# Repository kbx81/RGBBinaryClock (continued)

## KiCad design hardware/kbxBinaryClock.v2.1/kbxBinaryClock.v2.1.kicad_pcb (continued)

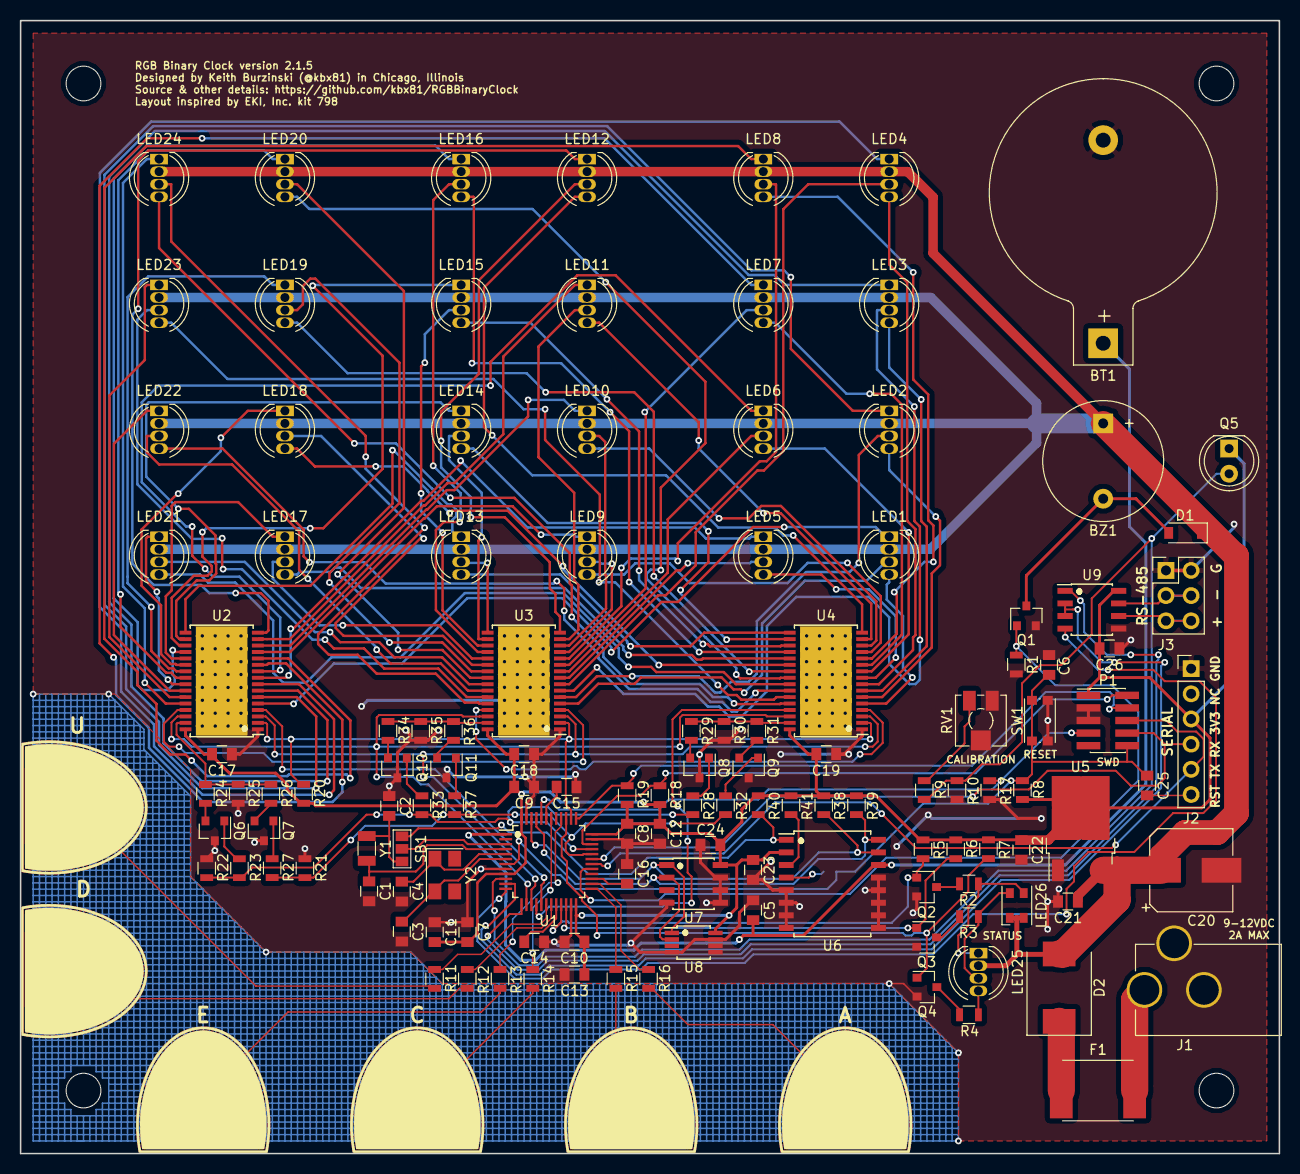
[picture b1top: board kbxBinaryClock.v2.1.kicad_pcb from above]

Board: 2 copper layers, 127.0 x 114.3 mm, 138 parts (1 on the bottom side), 152 nets.

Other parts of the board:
MH1, MH2, MH3, MH4: MountingHole_3.5mm

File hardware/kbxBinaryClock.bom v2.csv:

Reference (v2),Qty,Value,Footprint,Description,Documentation/Vendor
BT1,1,CR2032,Battery_Holders:Keystone_103_1x20mm-CoinCell,Battery cell,http://www.keyelco.com/product.cfm/product_id/719
BZ1,1,Buzzer,Buzzers_Beepers:Buzzer_12x9.5RM7.6,"Buzzer, polar",https://product.tdk.com/en/search/sw_piezo/sw_piezo/em-buzze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
"C1, C2",2,12.5 pF,Capacitors_SMD:C_0805,Unpolarized capacitor,
"C3, C4",2,10 pF,Capacitors_SMD:C_0805,Unpolarized capacitor,
"C5, C6, C8, C9, C10, C17, C18, C19, C21, C23, C24, C25, C26",13,100 nF,Capacitors_SMD:C_0805,Unpolarized capacitor,
C7,1,10 nF,Capacitors_SMD:C_0805,Unpolarized capacitor,
C11,1,1 µF,Capacitors_SMD:C_0805,Unpolarized capacitor,
"C12, C13",2,4.7 µF,Capacitors_SMD:C_0805,Unpolarized capacitor,
"C14, C15, C16",3,47 nF,Capacitors_SMD:C_0805,Unpolarized capacitor,
C20,1,100 µF,Capacitors_SMD:CP_Elec_8x10,Polarised capacitor,https://industrial.panasonic.com/ww/products/capacitors/poly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
C22,1,10 µF,Capacitors_SMD:C_0805,Unpolarized capacitor,
D1,1,1N4148,Diodes_SMD:D_SOD-123,Diode,https://www.diodes.com/assets/Datasheets/ds30086.pdf
D2,1,S3A,Diodes_SMD:D_SMC,,http://www.onsemi.com/pub/Collateral/S3N-D.PDF
F1,1,~2A Polyfuse,Fuse_Holders_and_Fuses:Fuse_SMD2920,"Resettable fuse, polymeric positive temperature coefficient (PPTC)",http://m.littelfuse.com/~/media/electronics/datasheets/reset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
J1,1,Jack-DC,BARREL_JACK,DC_Barrel Jack,
J2,1,Conn_01x06,Pin_Headers:Pin_Header_Straight_1x06_Pitch2.54mm,"Generic connector, single row, 01x06",
J3,1,Conn_02x03_Odd_Even,Pin_Headers:Pin_Header_Straight_2x03_Pitch2.54mm,"Generic connector, double row, 02x03",
"LED1, LED2, LED3, LED4, LED5, LED6, LED7, LED8, LED9, LED10, LED11, LED12, LED13, LED14, LED15, LED16, LED17, LED18, LED19, LED20, LED21, LED22, LED23, LED24, LED25",25,LED_RGB_COMMON_ANODE,LEDs:LED_D5.0mm-4,,https://www.adafruit.com/product/302
LED26,1,LED_Dual_AACC,LEDs:LED_Cree-PLCC4_3.2x2.8mm_CCW,"LED dual, 4-pin",https://www.vcclite.com/product/led-smt-1206-1-72-1v-20ma-re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
P1,1,STM32_SWD_USART,Pin_Headers:Pin_Header_Straight_2x05_Pitch1.27mm_SMD,,https://www.harwin.com/products/M50-3600542R/
"Q1, Q2, Q3, Q4",4,2N7002,TO_SOT_Packages_SMD:SOT-23,"50V Vds, 0.22 A Id, N-channel MOSFET, SOT-23",https://www.diodes.com/assets/Datasheets/ds11303.pdf
Q5,1,Q_Photo_NPN,LEDs:LED_D5.0mm,"Phototransistor NPN, 2-pin (C=1, E=2)",https://www.vishay.com/docs/84768/tept5600.pdf
"Q6, Q7, Q8, Q9, Q10, Q11",6,Q_NPN_BCE,TO_SOT_Packages_SMD:SOT-23,Transistor NPN (general),https://www.diodes.com/assets/Datasheets/ds30036.pdf
"R1, R5, R6, R7, R10",5,1M,Resistors_SMD:R_0805,Resistor,
"R2, R3, R4, R11, R12, R13, R14, R15, R16, R23, R27, R28, R32, R33, R37",15,1K,Resistors_SMD:R_0805,Resistor,
"R8, R9, R17, R18, R19, R20, R21, R22, R26, R31, R36, R40, R41",13,10K,Resistors_SMD:R_0805,Resistor,
"R24, R29, R34",3,4K7,Resistors_SMD:R_0805,Resistor,
"R25, R30, R35",3,24K6,Resistors_SMD:R_0805,Resistor,
"R38, R39",2,3K3,Resistors_SMD:R_0805,Resistor,
RV1,1,100K,Potentiometers:Potentiometer_Trimmer_Vishay_TS53YJ,Potentiometer,http://www.bourns.com/docs/Product-Datasheets/TC33.PDF
SW1,1,SW_Push,Buttons_Switches_SMD:SW_SPST_KMR2,"Push button switch, generic, two pins",https://www.ckswitches.com/media/1479/kmr2.pdf
U1,1,STM32F072CBTx,Housings_QFP:LQFP-48_7x7mm_Pitch0.5mm,Core: ARM Cortex-M0 Package: LQFP48 Flash: 128KB Ram: 16KB Frequency: 48MHz,http://www.st.com/content/ccc/resource/technical/document/da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
"U2, U3, U4",3,TLC5947,Housings_SSOP:HTSSOP-32_6.1x11mm_Pitch0.65mm_ThermalPad,,http://www.ti.com/lit/ds/symlink/tlc5947.pdf
U5,1,LD1117S33TR,TO_SOT_Packages_SMD:TO-252-2,"1A Low Dropout regulator, positive, 1.5V fixed output, SOT-223",http://www.st.com/content/ccc/resource/technical/document/da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
U6,1,DS3231,Housings_SOIC:SOIC-16W_7.5x10.3mm_Pitch1.27mm,Extremely Accurate I2C-Integrated RTC/TCXO/Crystal SOIC-16,https://datasheets.maximintegrated.com/en/ds/DS3231.pdf
U7,1,DS1621,Housings_SOIC:SOIC-8_3.9x4.9mm_Pitch1.27mm,LM75 compatible,https://datasheets.maximintegrated.com/en/ds/DS1621.pdf
U8,1,MCP9804,Housings_SSOP:MSOP-8_3x3mm_Pitch0.65mm,MCP9804/MCP9808,http://ww1.microchip.com/downloads/en/DeviceDoc/25095A.pdf
U9,1,MAX485E,Housings_SOIC:SOIC-8_3.9x4.9mm_Pitch1.27mm,"Half duplex RS-485/RS-422, 2.5 Mbps, ±15kV electro-static discharge (ESD) protection",http://www.st.com/content/ccc/resource/technical/document/da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
Y1,1,32.768 KHz,Crystals:Crystal_SMD_3215-2pin_3.2x1.5mm,Two pin crystal,https://www.ecsxtal.com/store/pdf/ECX-.327-CDX-1293.pdf
Y2,1,8 MHz,Crystals:Crystal_SMD_5032-4pin_5.0x3.2mm,Two pin crystal,http://www.abracon.com/Resonators/abm3b.pdf

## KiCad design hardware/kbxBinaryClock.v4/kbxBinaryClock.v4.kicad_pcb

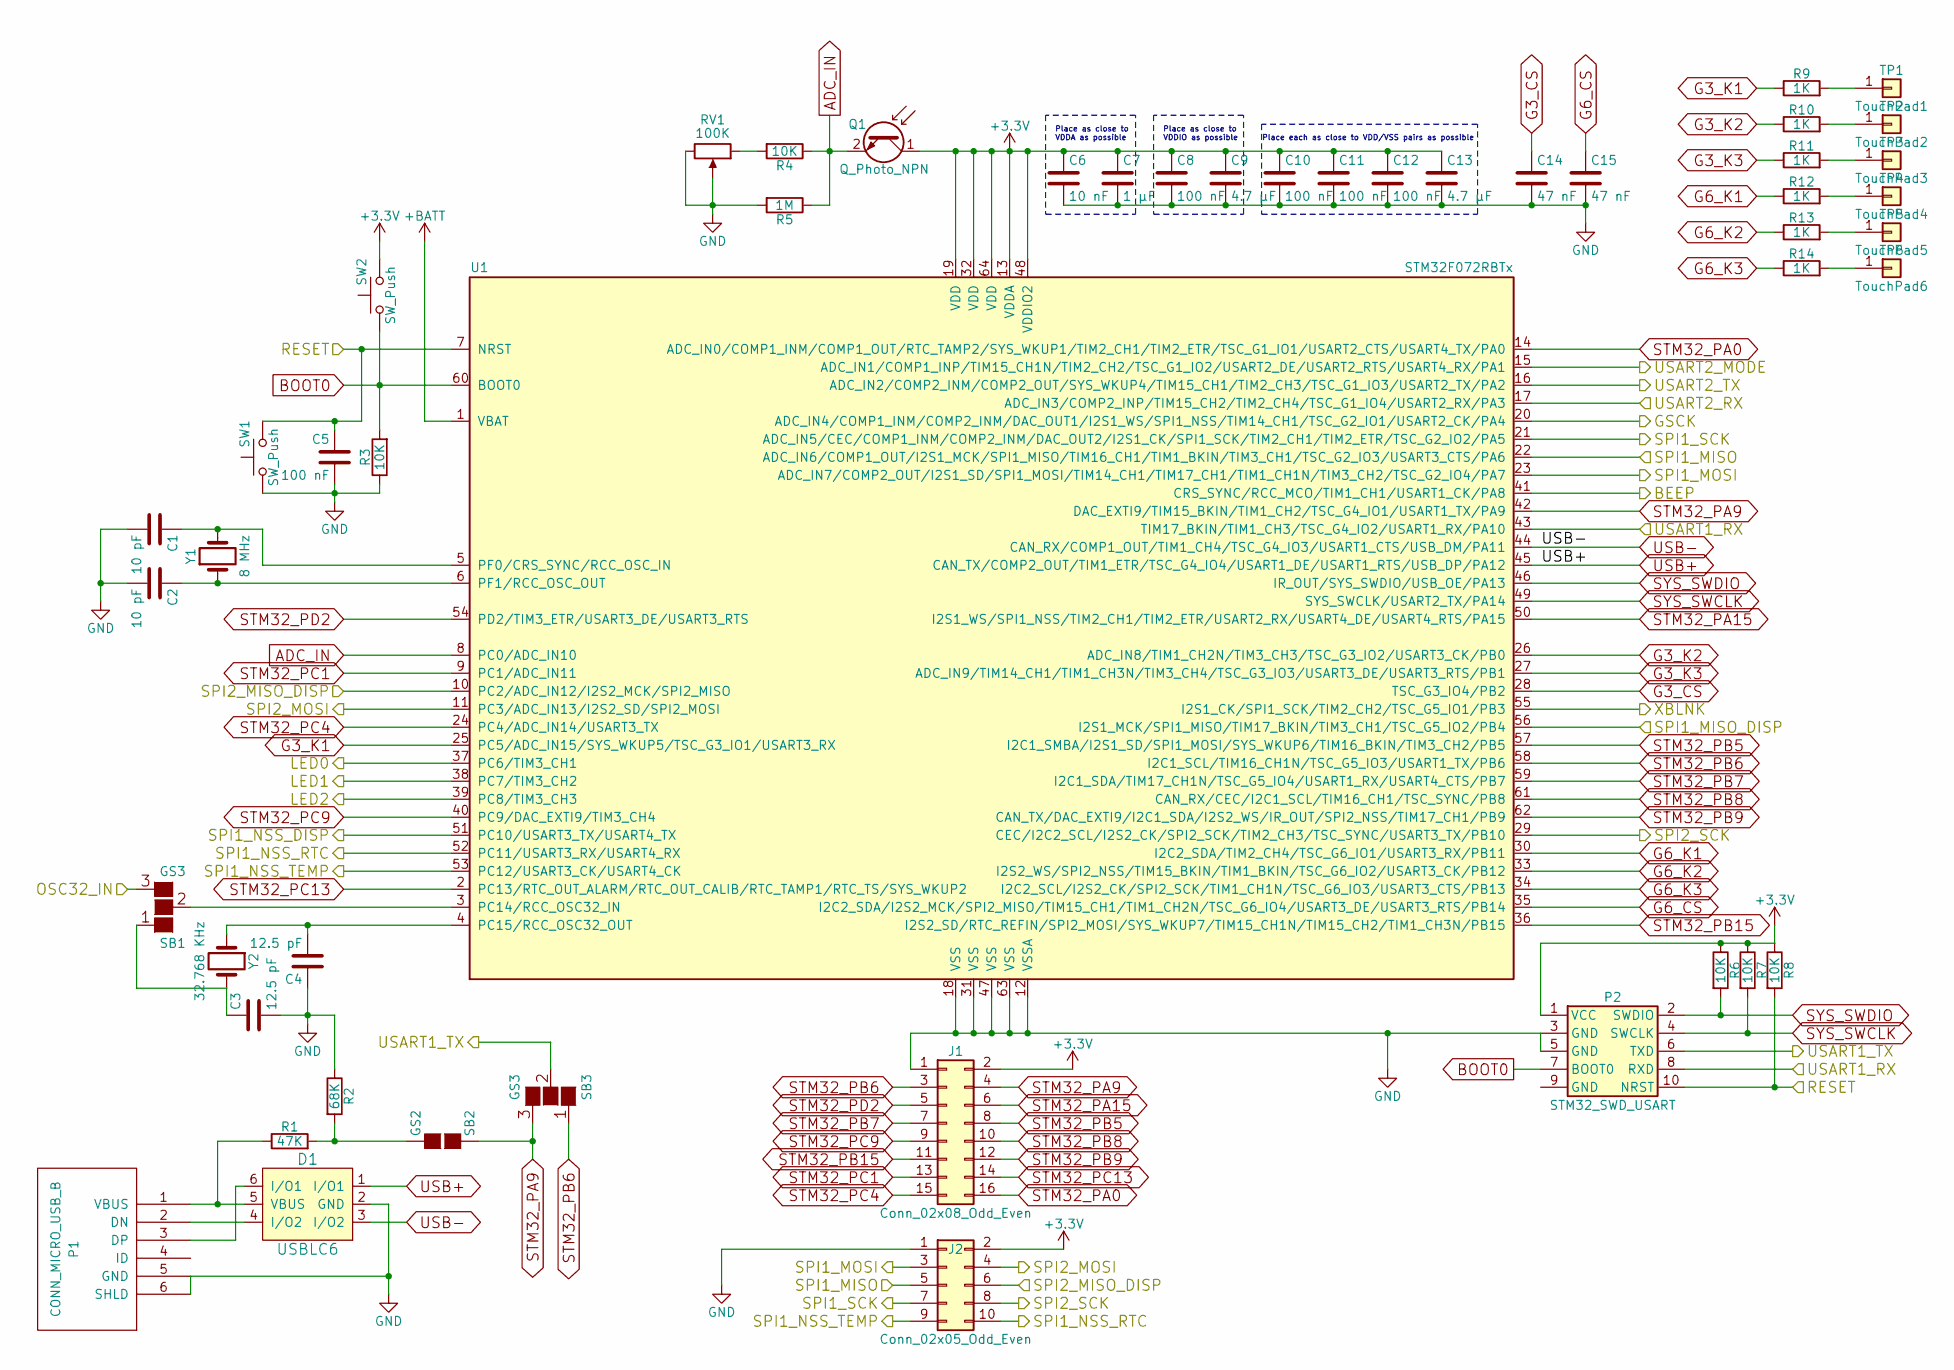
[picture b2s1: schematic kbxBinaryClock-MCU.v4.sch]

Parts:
C1, C2: 10 pF; C_0805
C3, C4: 12.5 pF; C_0805
C5, C8, C10, C11, C12: 100 nF; C_0805
C6: 10 nF; C_0805
C7: 1 µF; C_0805
C9, C13: 4.7 µF; C_0805
C14, C15: 47 nF; C_0805
D1: USBLC6; SOT-23-6
J1: Conn_02x08_Odd_Even; Pin_Header_Straight_2x08_Pitch2.54mm
J2: Conn_02x05_Odd_Even; Pin_Header_Straight_2x05_Pitch2.54mm
P1: CONN_MICRO_USB_B; USB_Micro-B_Molex-105017-0001
P2: STM32_SWD_USART; Pin_Header_Straight_2x05_Pitch1.27mm_SMD; Part Number M50-3600542R
Q1: Q_Photo_NPN; LED_D5.0mm; Part Number TEPT5600
R1: 47K; R_0805
R2: 68K; R_0805
R3, R4, R6, R7, R8: 10K; R_0805
R5: 1M; R_0805
R9, R10, R11, R12, R13, R14: 1K; R_0805
RV1: 100K; Potentiometer_Trimmer_Vishay_TS53YJ; Part Number TC33X-2-104E
SB1, SB3: GS3
SB2: GS2
SW1, SW2: SW_Push; SW_SPST_KMR2; Part Number KMR221G LFS
TP1: TouchPad1
TP2: TouchPad2; TouchPad1
TP3: TouchPad3; TouchPad1
TP4: TouchPad4; TouchPad1
TP5: TouchPad5; TouchPad1
TP6: TouchPad6; TouchPad1
U1: STM32F072RBTx; LQFP-64_10x10mm_Pitch0.5mm
Y1: 8 MHz; Crystal_SMD_5032-4pin_5.0x3.2mm; Part Number ABM3B-8.000MHZ-10-1UT
Y2: 32.768 KHz; Crystal_SMD_3215-2pin_3.2x1.5mm; Part Number ECX-.327-CDX-1293

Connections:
+3V3: C6.1, C7.1, C8.1, C9.1, C10.1, C11.1, C12.1, C13.1, J1.2, J2.2, P2.1 (VCC), Q1.1 (C), R6.1, R7.1, R8.1, SW2.2, U1.13 (VDDA), U1.19 (VDD), U1.32 (VDD), U1.48 (VDDIO2), U1.64 (VDD); also elsewhere on the board
+BATT: U1.1 (VBAT); also elsewhere on the board
/Display/GSCK: U1.20 (ADC_IN4/COMP1_INM/COMP2_INM/DAC_OUT1/I2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); also elsewhere on the board
/Display/SPI1_MISO_DISP: U1.56 (I2S1_MCK/SPI1_MISO/TIM17_BKIN/TIM3_CH1/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); also elsewhere on the board
/Display/SPI1_MOSI: J2.3, U1.23 (ADC_IN7/COMP2_OUT/I2S1_SD/SPI1_MOSI/TIM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); also elsewhere on the board
/Display/SPI1_NSS_DISP: U1.51 (PC10/USART3_TX/USART4_TX); also elsewhere on the board
/Display/SPI1_SCK: J2.7, U1.21 (ADC_IN5/CEC/COMP1_INM/COMP2_INM/DAC_OUT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); also elsewhere on the board
/Display/SPI2_MISO_DISP: J2.6, U1.10 (PC2/ADC_IN12/I2S2_MCK/SPI2_MISO); also elsewhere on the board
/Display/SPI2_MOSI: J2.4, U1.11 (PC3/ADC_IN13/I2S2_SD/SPI2_MOSI); also elsewhere on the board
/Display/SPI2_SCK: J2.8, U1.29 (CEC/I2C2_SCL/I2S2_CK/SPI2_SCK/TIM2_CH3/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); also elsewhere on the board
/Display/XBLNK: U1.55 (I2S1_CK/SPI1_SCK/TIM2_CH2/TSC_G5_IO1/PB3); also elsewhere on the board
/MCU/BEEP: U1.41 (CRS_SYNC/RCC_MCO/TIM1_CH1/USART1_CK/PA8); also elsewhere on the board
/MCU/LED0: U1.37 (PC6/TIM3_CH1); also elsewhere on the board
/MCU/LED1: U1.38 (PC7/TIM3_CH2); also elsewhere on the board
/MCU/LED2: U1.39 (PC8/TIM3_CH3); also elsewhere on the board
/MCU/OSC32_IN: SB1.3 (G3); also elsewhere on the board
/MCU/RESET: C5.1, P2.10 (NRST), R8.2, SW1.2, U1.7 (NRST); also elsewhere on the board
/MCU/SPI1_MISO: J2.5, U1.22 (ADC_IN6/COMP1_OUT/I2S1_MCK/SPI1_MISO/TI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); also elsewhere on the board
/MCU/SPI1_NSS_RTC: J2.10, U1.52 (PC11/USART3_RX/USART4_RX); also elsewhere on the board
/MCU/SPI1_NSS_TEMP: J2.9, U1.53 (PC12/USART3_CK/USART4_CK); also elsewhere on the board
/MCU/USART1_RX: P2.8 (RXD), U1.43 (TIM17_BKIN/TIM1_CH3/TSC_G4_IO2/USART1_R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); also elsewhere on the board
/MCU/USART1_TX: P2.6 (TXD), SB3.2 (G2); also elsewhere on the board
/MCU/USART2_MODE: U1.15 (ADC_IN1/COMP1_INP/TIM15_CH1N/TIM2_CH2/T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); also elsewhere on the board
/MCU/USART2_RX: U1.17 (ADC_IN3/COMP2_INP/TIM15_CH2/TIM2_CH4/TS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); also elsewhere on the board
/MCU/USART2_TX: U1.16 (ADC_IN2/COMP2_INM/COMP2_OUT/SYS_WKUP4/T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); also elsewhere on the board
ADC_IN: Q1.2 (E), R4.1, R5.1, U1.8 (PC0/ADC_IN10)
BOOT0: P2.7 (BOOT0), R3.2, SW2.1, U1.60 (BOOT0)
G3_CS: C14.1, U1.28 (TSC_G3_IO4/PB2)
G3_K1: R9.1, U1.25 (PC5/ADC_IN15/SYS_WKUP5/TSC_G3_IO1/USART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)
G3_K2: R10.1, U1.26 (ADC_IN8/TIM1_CH2N/TIM3_CH3/TSC_G3_IO2/U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)
G3_K3: R11.1, U1.27 (ADC_IN9/TIM14_CH1/TIM1_CH3N/TIM3_CH4/TS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)
G6_CS: C15.1, U1.35 (I2C2_SDA/I2S2_MCK/SPI2_MISO/TIM15_CH1/T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)
G6_K1: R12.1, U1.30 (I2C2_SDA/TIM2_CH4/TSC_G6_IO1/USART3_RX/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)
G6_K2: R13.1, U1.33 (I2S2_WS/SPI2_NSS/TIM15_BKIN/TIM1_BKIN/T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)
G6_K3: R14.1, U1.34 (I2C2_SCL/I2S2_CK/SPI2_SCK/TIM1_CH1N/TSC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)
GND: C1.2, C2.2, C3.2, C4.1, C5.2, C6.2, C7.2, C8.2, C9.2, C10.2, C11.2, C12.2, C13.2, C14.2, C15.2, D1.2 (GND), J1.1, J2.1, P1.5 (GND), P1.6 (SHLD), P2.3 (GND), P2.5 (GND), R2.1, R3.1, R5.2, RV1.2, RV1.3, SW1.1, U1.12 (VSSA), U1.18 (VSS), U1.31 (VSS), U1.47 (VSS), U1.63 (VSS); also elsewhere on the board
unnamed: C1.1, U1.5 (PF0/CRS_SYNC/RCC_OSC_IN), Y1.2
unnamed: C2.1, U1.6 (PF1/RCC_OSC_OUT), Y1.1
unnamed: C3.1, SB1.1 (G1), Y2.2
unnamed: C4.2, U1.4 (PC15/RCC_OSC32_OUT), Y2.1
unnamed: D1.4 (I/O2), P1.2 (DN)
unnamed: D1.5 (VBUS), P1.1 (VBUS), R1.1
unnamed: D1.6 (I/O1), P1.3 (DP)
unnamed: R1.2, R2.2, SB2.2 (G2)
unnamed: R4.2, RV1.1
unnamed: R9.2, TP1.1
unnamed: R10.2, TP2.1
unnamed: R11.2, TP3.1
unnamed: R12.2, TP4.1
unnamed: R13.2, TP5.1
unnamed: R14.2, TP6.1
unnamed: SB1.2 (G2), U1.3 (PC14/RCC_OSC32_IN)
STM32_PA0: J1.16, U1.14 (ADC_IN0/COMP1_INM/COMP1_OUT/RTC_TAMP2/S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)
STM32_PA9: J1.4, SB2.1 (G1), SB3.3 (G3), U1.42 (DAC_EXTI9/TIM15_BKIN/TIM1_CH2/TSC_G4_IO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)
STM32_PA15: J1.6, U1.50 (I2S1_WS/SPI1_NSS/TIM2_CH1/TIM2_ETR/USAR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)
STM32_PB5: J1.8, U1.57 (I2C1_SMBA/I2S1_SD/SPI1_MOSI/SYS_WKUP6/T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)
STM32_PB6: J1.3, SB3.1 (G1), U1.58 (I2C1_SCL/TIM16_CH1N/TSC_G5_IO3/USART1_T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)
STM32_PB7: J1.7, U1.59 (I2C1_SDA/TIM17_CH1N/TSC_G5_IO4/USART1_R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)
STM32_PB8: J1.10, U1.61 (CAN_RX/CEC/I2C1_SCL/TIM16_CH1/TSC_SYNC/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)
STM32_PB9: J1.12, U1.62 (CAN_TX/DAC_EXTI9/I2C1_SDA/I2S2_WS/IR_OU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)
STM32_PB15: J1.11, U1.36 (I2S2_SD/RTC_REFIN/SPI2_MOSI/SYS_WKUP7/T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)
STM32_PC1: J1.13, U1.9 (PC1/ADC_IN11)
STM32_PC4: J1.15, U1.24 (PC4/ADC_IN14/USART3_TX)
STM32_PC9: J1.9, U1.40 (PC9/DAC_EXTI9/TIM3_CH4)
STM32_PC13: J1.14, U1.2 (PC13/RTC_OUT_ALARM/RTC_OUT_CALIB/RTC_TA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)
STM32_PD2: J1.5, U1.54 (PD2/TIM3_ETR/USART3_DE/USART3_RTS)
SYS_SWCLK: P2.4 (SWCLK), R7.2, U1.49 (SYS_SWCLK/USART2_TX/PA14)
SYS_SWDIO: P2.2 (SWDIO), R6.2, U1.46 (IR_OUT/SYS_SWDIO/USB_OE/PA13)
USB+: D1.1 (I/O1), U1.45 (CAN_TX/COMP2_OUT/TIM1_ETR/TSC_G4_IO4/US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)
USB-: D1.3 (I/O2), U1.44 (CAN_RX/COMP1_OUT/TIM1_CH4/TSC_G4_IO3/US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)

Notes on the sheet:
Place as close to VDDA as possible
Place as close to VDDIO as possible
Place each as close to VDD/VSS pairs as possible

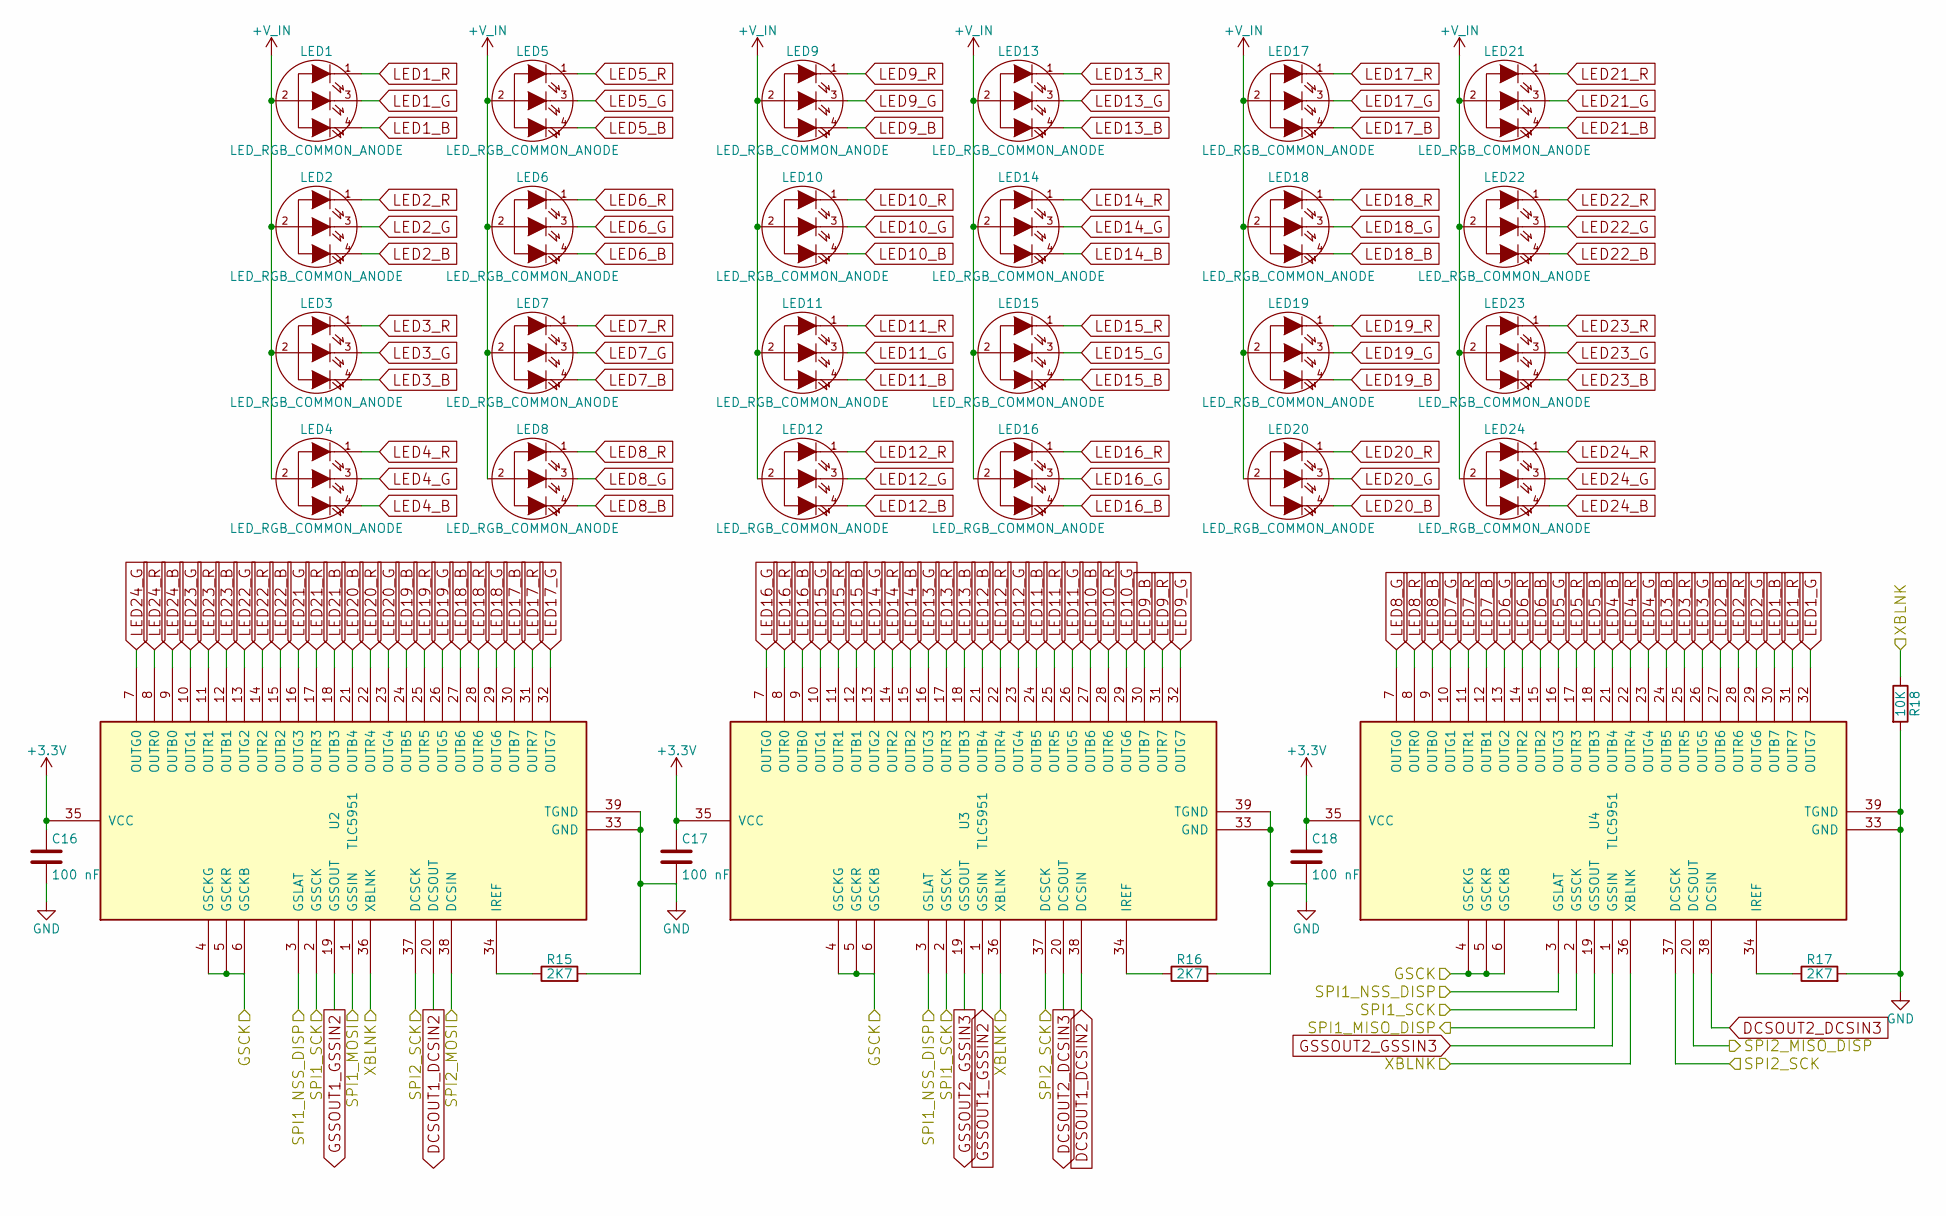
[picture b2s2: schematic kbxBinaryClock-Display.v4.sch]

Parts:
C16, C17, C18: 100 nF; C_0805
LED1, LED2, LED3, LED4, LED5, LED6, LED7, LED8, LED9, LED10, LED11, LED12, LED13, LED14, LED15, LED16, LED17, LED18, LED19, LED20, LED21, LED22, LED23, LED24: LED_RGB_COMMON_ANODE; LED_D5.0mm-4
R15, R16, R17: 2K7; R_0805
R18: 10K; R_0805
U2, U3, U4: TLC5951; HTSSOP-38_6.1x12.5mm_Pitch0.65mm_ThermalPad

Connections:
+3V3: C16.1, C17.1, C18.1, U2.35 (VCC), U3.35 (VCC), U4.35 (VCC); also elsewhere on the board
+V_IN: LED1.2 (COMMON), LED2.2 (COMMON), LED3.2 (COMMON), LED4.2 (COMMON), LED5.2 (COMMON), LED6.2 (COMMON), LED7.2 (COMMON), LED8.2 (COMMON), LED9.2 (COMMON), LED10.2 (COMMON), LED11.2 (COMMON), LED12.2 (COMMON), LED13.2 (COMMON), LED14.2 (COMMON), LED15.2 (COMMON), LED16.2 (COMMON), LED17.2 (COMMON), LED18.2 (COMMON), LED19.2 (COMMON), LED20.2 (COMMON), LED21.2 (COMMON), LED22.2 (COMMON), LED23.2 (COMMON), LED24.2 (COMMON); also elsewhere on the board
/Display/GSCK: U2.4 (GSCKG), U2.5 (GSCKR), U2.6 (GSCKB), U3.4 (GSCKG), U3.5 (GSCKR), U3.6 (GSCKB), U4.4 (GSCKG), U4.5 (GSCKR), U4.6 (GSCKB); also elsewhere on the board
/Display/SPI1_MISO_DISP: U4.19 (GSSOUT); also elsewhere on the board
/Display/SPI1_MOSI: U2.1 (GSSIN); also elsewhere on the board
/Display/SPI1_NSS_DISP: U2.3 (GSLAT), U3.3 (GSLAT), U4.3 (GSLAT); also elsewhere on the board
/Display/SPI1_SCK: U2.2 (GSSCK), U3.2 (GSSCK), U4.2 (GSSCK); also elsewhere on the board
/Display/SPI2_MISO_DISP: U4.20 (DCSOUT); also elsewhere on the board
/Display/SPI2_MOSI: U2.38 (DCSIN); also elsewhere on the board
/Display/SPI2_SCK: U2.37 (DCSCK), U3.37 (DCSCK), U4.37 (DCSCK); also elsewhere on the board
/Display/XBLNK: R18.1, U2.36 (XBLNK), U3.36 (XBLNK), U4.36 (XBLNK); also elsewhere on the board
DCSOUT1_DCSIN2: U2.20 (DCSOUT), U3.38 (DCSIN)
DCSOUT2_DCSIN3: U3.20 (DCSOUT), U4.38 (DCSIN)
GND: C16.2, C17.2, C18.2, R15.2, R16.2, R17.2, R18.2, U2.33 (GND), U2.39 (TGND), U3.33 (GND), U3.39 (TGND), U4.33 (GND), U4.39 (TGND); also elsewhere on the board
GSSOUT1_GSSIN2: U2.19 (GSSOUT), U3.1 (GSSIN)
GSSOUT2_GSSIN3: U3.19 (GSSOUT), U4.1 (GSSIN)
LED1_B: LED1.4 (BLUE), U4.30 (OUTB7)
LED1_G: LED1.3 (GREEN), U4.32 (OUTG7)
LED1_R: LED1.1 (RED), U4.31 (OUTR7)
LED2_B: LED2.4 (BLUE), U4.27 (OUTB6)
LED2_G: LED2.3 (GREEN), U4.29 (OUTG6)
LED2_R: LED2.1 (RED), U4.28 (OUTR6)
LED3_B: LED3.4 (BLUE), U4.24 (OUTB5)
LED3_G: LED3.3 (GREEN), U4.26 (OUTG5)
LED3_R: LED3.1 (RED), U4.25 (OUTR5)
LED4_B: LED4.4 (BLUE), U4.21 (OUTB4)
LED4_G: LED4.3 (GREEN), U4.23 (OUTG4)
LED4_R: LED4.1 (RED), U4.22 (OUTR4)
LED5_B: LED5.4 (BLUE), U4.18 (OUTB3)
LED5_G: LED5.3 (GREEN), U4.16 (OUTG3)
LED5_R: LED5.1 (RED), U4.17 (OUTR3)
LED6_B: LED6.4 (BLUE), U4.15 (OUTB2)
LED6_G: LED6.3 (GREEN), U4.13 (OUTG2)
LED6_R: LED6.1 (RED), U4.14 (OUTR2)
LED7_B: LED7.4 (BLUE), U4.12 (OUTB1)
LED7_G: LED7.3 (GREEN), U4.10 (OUTG1)
LED7_R: LED7.1 (RED), U4.11 (OUTR1)
LED8_B: LED8.4 (BLUE), U4.9 (OUTB0)
LED8_G: LED8.3 (GREEN), U4.7 (OUTG0)
LED8_R: LED8.1 (RED), U4.8 (OUTR0)
LED9_B: LED9.4 (BLUE), U3.30 (OUTB7)
LED9_G: LED9.3 (GREEN), U3.32 (OUTG7)
LED9_R: LED9.1 (RED), U3.31 (OUTR7)
LED10_B: LED10.4 (BLUE), U3.27 (OUTB6)
LED10_G: LED10.3 (GREEN), U3.29 (OUTG6)
LED10_R: LED10.1 (RED), U3.28 (OUTR6)
LED11_B: LED11.4 (BLUE), U3.24 (OUTB5)
LED11_G: LED11.3 (GREEN), U3.26 (OUTG5)
LED11_R: LED11.1 (RED), U3.25 (OUTR5)
LED12_B: LED12.4 (BLUE), U3.21 (OUTB4)
LED12_G: LED12.3 (GREEN), U3.23 (OUTG4)
LED12_R: LED12.1 (RED), U3.22 (OUTR4)
LED13_B: LED13.4 (BLUE), U3.18 (OUTB3)
LED13_G: LED13.3 (GREEN), U3.16 (OUTG3)
LED13_R: LED13.1 (RED), U3.17 (OUTR3)
LED14_B: LED14.4 (BLUE), U3.15 (OUTB2)
LED14_G: LED14.3 (GREEN), U3.13 (OUTG2)
LED14_R: LED14.1 (RED), U3.14 (OUTR2)
LED15_B: LED15.4 (BLUE), U3.12 (OUTB1)
LED15_G: LED15.3 (GREEN), U3.10 (OUTG1)
LED15_R: LED15.1 (RED), U3.11 (OUTR1)
LED16_B: LED16.4 (BLUE), U3.9 (OUTB0)
LED16_G: LED16.3 (GREEN), U3.7 (OUTG0)
LED16_R: LED16.1 (RED), U3.8 (OUTR0)
LED17_B: LED17.4 (BLUE), U2.30 (OUTB7)
LED17_G: LED17.3 (GREEN), U2.32 (OUTG7)
LED17_R: LED17.1 (RED), U2.31 (OUTR7)
LED18_B: LED18.4 (BLUE), U2.27 (OUTB6)
LED18_G: LED18.3 (GREEN), U2.29 (OUTG6)
LED18_R: LED18.1 (RED), U2.28 (OUTR6)
LED19_B: LED19.4 (BLUE), U2.24 (OUTB5)
LED19_G: LED19.3 (GREEN), U2.26 (OUTG5)
LED19_R: LED19.1 (RED), U2.25 (OUTR5)
LED20_B: LED20.4 (BLUE), U2.21 (OUTB4)
LED20_G: LED20.3 (GREEN), U2.23 (OUTG4)
LED20_R: LED20.1 (RED), U2.22 (OUTR4)
LED21_B: LED21.4 (BLUE), U2.18 (OUTB3)
LED21_G: LED21.3 (GREEN), U2.16 (OUTG3)
LED21_R: LED21.1 (RED), U2.17 (OUTR3)
LED22_B: LED22.4 (BLUE), U2.15 (OUTB2)
LED22_G: LED22.3 (GREEN), U2.13 (OUTG2)
LED22_R: LED22.1 (RED), U2.14 (OUTR2)
LED23_B: LED23.4 (BLUE), U2.12 (OUTB1)
LED23_G: LED23.3 (GREEN), U2.10 (OUTG1)
LED23_R: LED23.1 (RED), U2.11 (OUTR1)
LED24_B: LED24.4 (BLUE), U2.9 (OUTB0)
LED24_G: LED24.3 (GREEN), U2.7 (OUTG0)
LED24_R: LED24.1 (RED), U2.8 (OUTR0)
unnamed: R15.1, U2.34 (IREF)
unnamed: R16.1, U3.34 (IREF)
unnamed: R17.1, U4.34 (IREF)

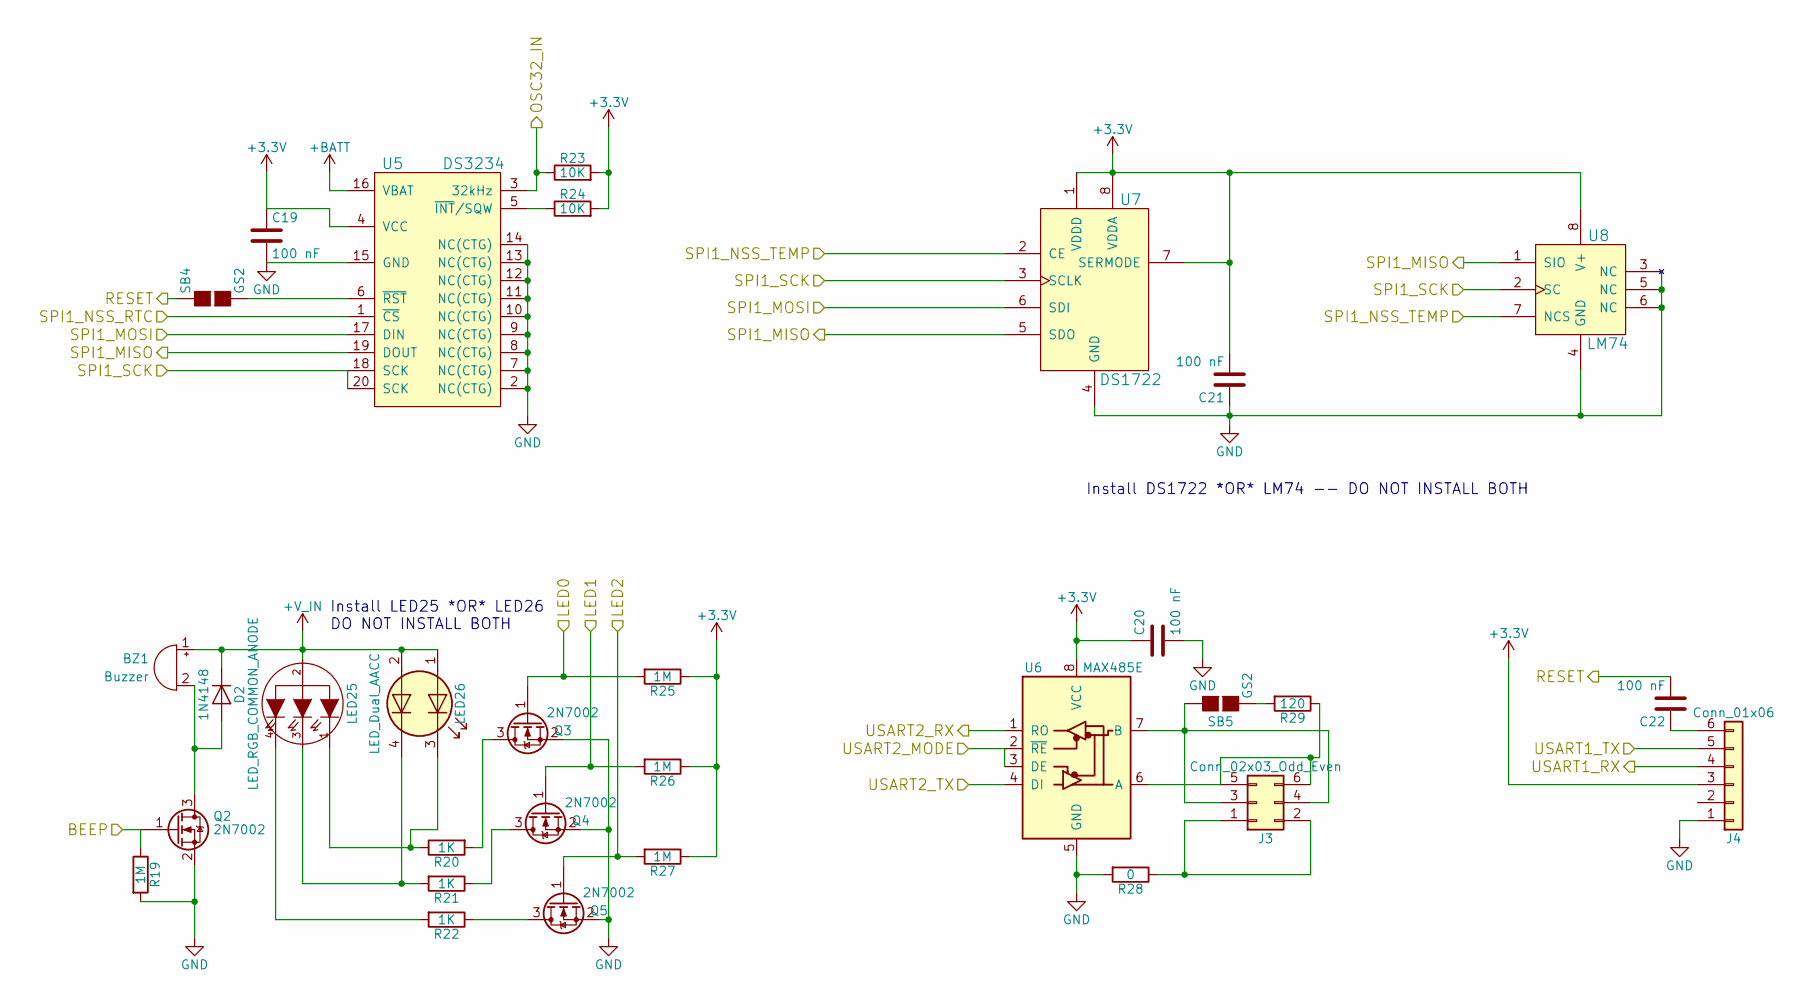
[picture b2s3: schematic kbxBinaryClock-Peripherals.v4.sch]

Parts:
BZ1: Buzzer; Buzzer_12x9.5RM7.6; Part Number TDK SD1614TT-B1
C19, C20, C21, C22: 100 nF; C_0805
D2: 1N4148; D_SOD-123
J3: Conn_02x03_Odd_Even; Pin_Header_Straight_2x03_Pitch2.54mm
J4: Conn_01x06; Pin_Header_Straight_1x06_Pitch2.54mm
LED25: LED_RGB_COMMON_ANODE; LED_D5.0mm-4
LED26: LED_Dual_AACC; LED_Cree-PLCC4_3.2x2.8mm_CCW; Part Number CMD1522SRUGCTR8
Q2, Q3, Q4, Q5: 2N7002; SOT-23
R19, R25, R26, R27: 1M; R_0805
R20, R21, R22: 1K; R_0805
R23, R24: 10K; R_0805
R28: 0; R_0805
R29: 120; R_0805
SB4, SB5: GS2
U5: DS3234; SO-20_12.8x7.5mm_Pitch1.27mm
U6: MAX485E; SOIC-8_3.9x4.9mm_Pitch1.27mm; Part Number ST1480ACDR
U7: DS1722; SOIC-8_3.9x4.9mm_Pitch1.27mm
U8: LM74; SOIC-8_3.9x4.9mm_Pitch1.27mm; Part Number LM74CIMX-3/NOPB

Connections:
+3V3: C19.1, C20.1, C21.2, J4.3, R23.2, R24.2, R25.1, R26.1, R27.1, U5.4 (VCC), U6.8 (VCC), U7.1 (VDDD), U7.7 (SERMODE), U7.8 (VDDA), U8.8 (V+); also elsewhere on the board
+BATT: U5.16 (VBAT); also elsewhere on the board
+V_IN: BZ1.1 (-), D2.1 (K), LED25.2 (COMMON), LED26.1 (A1), LED26.2 (A2); also elsewhere on the board
/Display/SPI1_MOSI: U5.17 (DIN), U7.6 (SDI); also elsewhere on the board
/Display/SPI1_SCK: U5.18 (SCK), U5.20 (SCK), U7.3 (SCLK), U8.2 (SC); also elsewhere on the board
/MCU/BEEP: Q2.1 (G), R19.1; also elsewhere on the board
/MCU/LED0: Q3.1 (G), R25.2; also elsewhere on the board
/MCU/LED1: Q4.1 (G), R26.2; also elsewhere on the board
/MCU/LED2: Q5.1 (G), R27.2; also elsewhere on the board
/MCU/OSC32_IN: R23.1, U5.3 (32kHz); also elsewhere on the board
/MCU/RESET: C22.2, SB4.1 (G1); also elsewhere on the board
/MCU/SPI1_MISO: U5.19 (DOUT), U7.5 (SDO), U8.1 (SIO); also elsewhere on the board
/MCU/SPI1_NSS_RTC: U5.1 (~CS~); also elsewhere on the board
/MCU/SPI1_NSS_TEMP: U7.2 (CE), U8.7 (NCS); also elsewhere on the board
/MCU/USART1_RX: J4.4; also elsewhere on the board
/MCU/USART1_TX: J4.5; also elsewhere on the board
/MCU/USART2_MODE: U6.2 (~RE), U6.3 (DE); also elsewhere on the board
/MCU/USART2_RX: U6.1 (RO); also elsewhere on the board
/MCU/USART2_TX: U6.4 (DI); also elsewhere on the board
GND: C19.2, C20.2, C21.1, J4.1, Q2.2 (S), Q3.2 (S), Q4.2 (S), Q5.2 (S), R19.2, R28.2, U5.2 (NC(CTG)), U5.7 (NC(CTG)), U5.8 (NC(CTG)), U5.9 (NC(CTG)), U5.10 (NC(CTG)), U5.11 (NC(CTG)), U5.12 (NC(CTG)), U5.13 (NC(CTG)), U5.14 (NC(CTG)), U5.15 (GND), U6.5 (GND), U7.4 (GND), U8.3 (NC), U8.4 (GND), U8.5 (NC), U8.6 (NC); also elsewhere on the board
unnamed: BZ1.2 (+), D2.2 (A), Q2.3 (D)
unnamed: C22.1, J4.6
unnamed: J3.1, J3.2, R28.1
unnamed: J3.3, J3.4, SB5.1 (G1), U6.7 (B)
unnamed: J3.5, J3.6, R29.1, U6.6 (A)
unnamed: LED25.1 (RED), LED26.3 (K1), R20.1
unnamed: LED25.3 (GREEN), LED26.4 (K2), R21.2
unnamed: LED25.4 (BLUE), R22.2
unnamed: Q3.3 (D), R20.2
unnamed: Q4.3 (D), R21.1
unnamed: Q5.3 (D), R22.1
unnamed: R24.1, U5.5 (~INT~/SQW)
unnamed: R29.2, SB5.2 (G2)
unnamed: SB4.2 (G2), U5.6 (~RST~)

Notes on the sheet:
Install DS1722 *OR* LM74 -- DO NOT INSTALL BOTH
Install LED25 *OR* LED26 DO NOT INSTALL BOTH

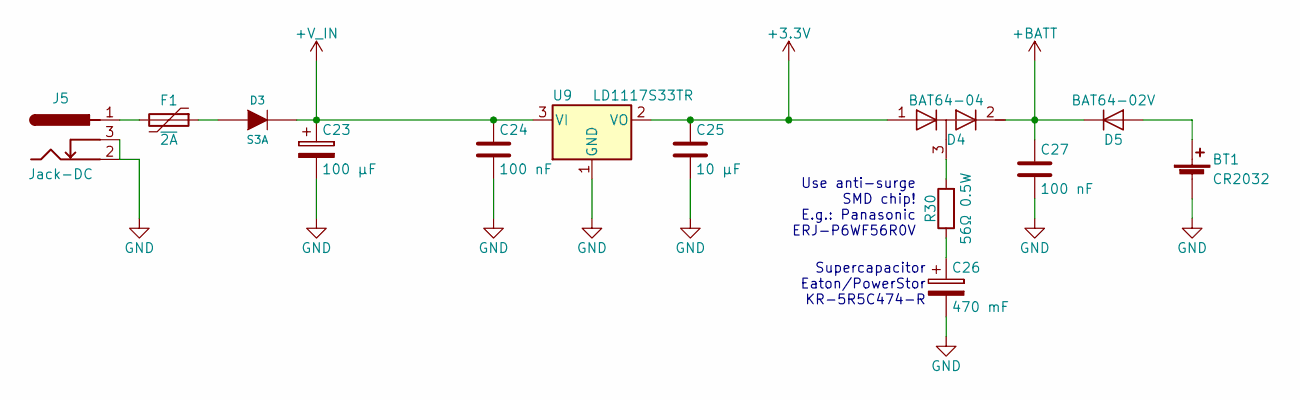
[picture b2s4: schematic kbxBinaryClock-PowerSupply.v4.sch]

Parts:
BT1: CR2032; Keystone_103_1x20mm-CoinCell; Part Number 103
C23: 100 µF; CP_Elec_8x10; Part Number 25SVF100M
C24, C27: 100 nF; C_0805
C25: 10 µF; C_0805
C26: 470 mF; CP_Radial_D13.0mm_P5.00mm_HD1.5mm; Part Number KR-5R5H474-R
D3: S3A; D_SMC; Part Number S3A
D4: BAT64-04; SOT-23
D5: BAT64-02V; D_0603
F1: ~2A; Fuse_SMD2920; Part Number 2920L185DR
J5: Jack-DC; BARREL_JACK
R30: 56Ω 0.5W; R_0805
U9: LD1117S33TR; TO-252-2; Part Number LD1117ADT33TR

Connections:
+3V3: C25.1, D4.1 (A), U9.2 (VO); also elsewhere on the board
+BATT: C27.1, D4.2 (K), D5.1 (K); also elsewhere on the board
+V_IN: C23.1, C24.1, D3.2 (K), U9.3 (VI); also elsewhere on the board
GND: BT1.2 (-), C23.2, C24.2, C25.2, C26.2, C27.2, J5.2, J5.3, U9.1 (GND); also elsewhere on the board
unnamed: BT1.1 (+), D5.2 (A)
unnamed: C26.1, R30.1
unnamed: D3.1 (A), F1.1
unnamed: D4.3 (common), R30.2
unnamed: F1.2, J5.1

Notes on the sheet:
Supercapacitor Eaton/PowerStor KR-5R5C474-R
Use anti-surge SMD chip! E.g.: Panasonic ERJ-P6WF56R0V
